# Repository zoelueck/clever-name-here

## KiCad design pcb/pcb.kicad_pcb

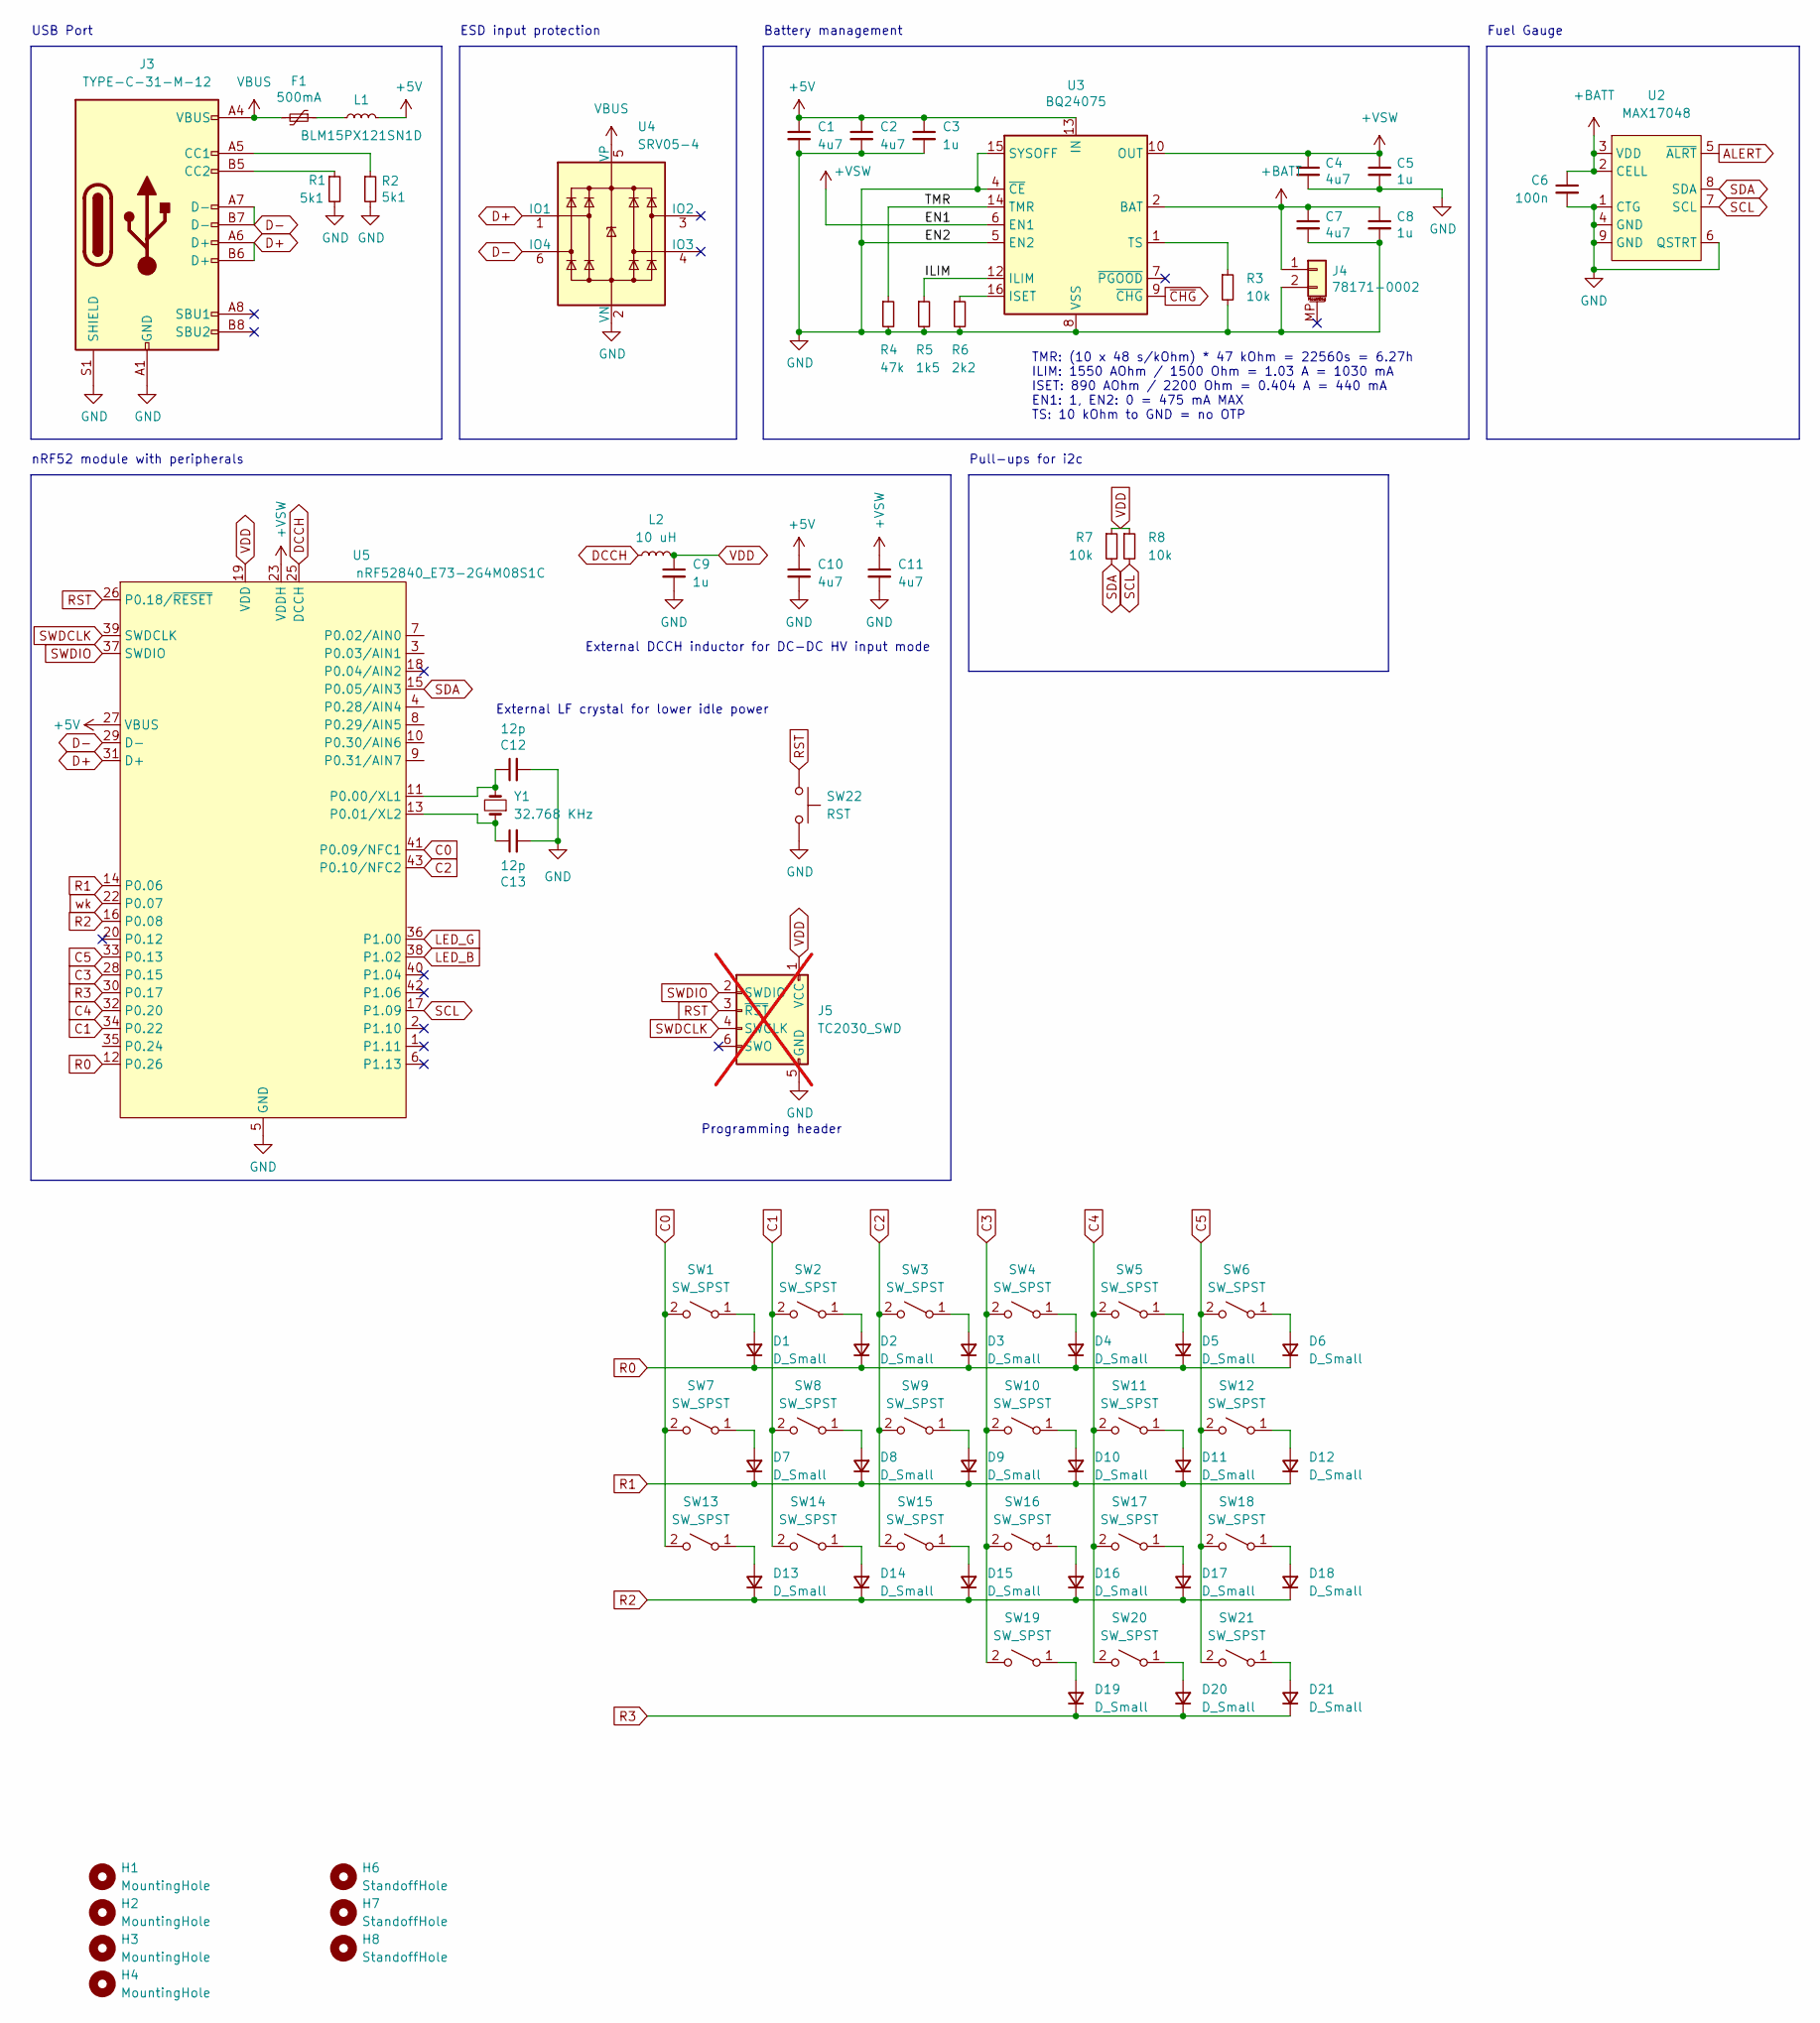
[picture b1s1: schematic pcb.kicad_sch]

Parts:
C1, C2, C4, C7, C10, C11: 4u7; C_0402_1005Metric; LCSC C23733
C3, C5, C8, C9: 1u; C_0402_1005Metric; LCSC C52923
C6: 100n; C_0402_1005Metric; LCSC C307331
C12, C13: 12p; C_0402_1005Metric; LCSC C1547
D1, D2, D3, D4, D5, D6, D7, D8, D9, D10, D11, D12, D13, D14, D15, D16, D17, D18, D19, D20, D21: D_Small; Diode_TH_SMD_DUAL
F1: 500mA; Fuse_0603_1608Metric; LCSC C883095
H1, H2, H3, H4: MountingHole; Hole_4.2mm
H6, H7, H8: StandoffHole; Hole_2.2mm
J3: TYPE-C-31-M-12; USB_C_Receptacle_HRO_TYPE-C-31-M-12; LCSC C165948
J4: 78171-0002; Molex_Pico-EZmate_78171-0002_1x02-1MP_P1.20mm_Vertical; LCSC C505023
J5: TC2030_SWD; CON_TC2030_outlined; not fitted
L1: BLM15PX121SN1D; L_0402_1005Metric; LCSC C88970
L2: 10 uH; L_0603_1608Metric; LCSC C92982
R1, R2: 5k1; R_0402_1005Metric; LCSC C25905
R3, R7, R8: 10k; R_0402_1005Metric; LCSC C25744
R4: 47k; R_0402_1005Metric; LCSC C25792
R5: 1k5; R_0402_1005Metric; LCSC C25867
R6: 2k2; R_0402_1005Metric; LCSC C25879
SW1, SW2, SW3, SW4, SW5, SW6, SW7, SW8, SW9, SW10, SW11, SW12, SW13, SW14, SW15, SW16, SW17, SW18, SW19, SW20, SW21: SW_SPST; KS-27_KS-33_Hotswap_1U_DUAL
SW22: RST; SW_T1A2QR; LCSC C100056
U2: MAX17048; DFN-8-1EP_2x2mm_P0.5mm_EP0.7x1.3mm; LCSC C2682616
U3: BQ24075; VQFN-16-1EP_3x3mm_P0.5mm_EP1.6x1.6mm; LCSC C15464
U4: SRV05-4; SOT-23-6-routable; LCSC C7420376
U5: nRF52840_E73-2G4M08S1C; LCSC C356849
Y1: 32.768 KHz; Crystal_SMD_2012-2Pin_2.0x1.2mm; LCSC C55208

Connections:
+5V: C1.1, C2.1, C3.1, C10.1, L1.2, U3.13 (IN), U5.27 (VBUS)
+BATT: C6.1, C7.1, C8.1, J4.1, U2.2 (CELL), U2.3 (VDD), U3.2 (BAT), U3.3 (BAT)
+VSW: C4.1, C5.1, C11.1, U3.6 (EN1), U3.10 (OUT), U3.11 (OUT), U5.23 (VDDH)
/ILIM: R5.1, U3.12 (ILIM)
/TMR: R4.1, U3.14 (TMR)
ALERT: U2.5 (~ALRT)
C0: SW1.2 (B), SW7.2 (B), SW13.2 (B), U5.41 (P0.09/NFC1)
C1: SW2.2 (B), SW8.2 (B), SW14.2 (B), U5.34 (P0.22)
C2: SW3.2 (B), SW9.2 (B), SW15.2 (B), U5.43 (P0.10/NFC2)
C3: SW4.2 (B), SW10.2 (B), SW16.2 (B), SW19.2 (B), U5.28 (P0.15)
C4: SW5.2 (B), SW11.2 (B), SW17.2 (B), SW20.2 (B), U5.32 (P0.20)
C5: SW6.2 (B), SW12.2 (B), SW18.2 (B), SW21.2 (B), U5.33 (P0.13)
D+: J3.A6 (D+), J3.B6 (D+), U4.1 (IO1), U5.31 (D+)
D-: J3.A7 (D-), J3.B7 (D-), U4.6 (IO4), U5.29 (D-)
DCCH: L2.1, U5.25 (DCCH)
GND: C1.2, C2.2, C3.2, C4.2, C5.2, C6.2, C7.2, C8.2, C9.2, C10.2, C11.2, C12.2, C13.2, J3.A1 (GND), J3.A12 (GND), J3.B1 (GND), J3.B12 (GND), J3.S1 (SHIELD), J4.2, J5.5 (GND), R1.2, R2.2, R3.2, R4.2, R5.2, R6.2, SW22.2, U2.1 (CTG), U2.4 (GND), U2.6 (QSTRT), U2.9 (GND), U3.4 (~CE), U3.5 (EN2), U3.8 (VSS), U3.15 (SYSOFF), U3.17 (VSS), U4.2 (VN), U5.5 (GND), U5.21 (GND), U5.24 (GND)
LED_B: U5.38 (P1.02)
LED_G: U5.36 (P1.00)
unnamed: D1.2 (A), SW1.1 (A)
unnamed: D2.2 (A), SW2.1 (A)
unnamed: D3.2 (A), SW3.1 (A)
unnamed: D4.2 (A), SW4.1 (A)
unnamed: D5.2 (A), SW5.1 (A)
unnamed: D6.2 (A), SW6.1 (A)
unnamed: D7.2 (A), SW7.1 (A)
unnamed: D8.2 (A), SW8.1 (A)
unnamed: D9.2 (A), SW9.1 (A)
unnamed: D10.2 (A), SW10.1 (A)
unnamed: D11.2 (A), SW11.1 (A)
unnamed: D12.2 (A), SW12.1 (A)
unnamed: D13.2 (A), SW13.1 (A)
unnamed: D14.2 (A), SW14.1 (A)
unnamed: D15.2 (A), SW15.1 (A)
unnamed: D16.2 (A), SW16.1 (A)
unnamed: D17.2 (A), SW17.1 (A)
unnamed: D18.2 (A), SW18.1 (A)
unnamed: D19.2 (A), SW19.1 (A)
unnamed: D20.2 (A), SW20.1 (A)
unnamed: D21.2 (A), SW21.1 (A)
unnamed: F1.1, L1.1
unnamed: J3.A5 (CC1), R2.1
unnamed: J3.B5 (CC2), R1.1
unnamed: R6.1, U3.16 (ISET)
unnamed: R3.1, U3.1 (TS)
unnamed: C12.1, U5.11 (P0.00/XL1), Y1.2
unnamed: C13.1, U5.13 (P0.01/XL2), Y1.1
R0: D1.1 (K), D2.1 (K), D3.1 (K), D4.1 (K), D5.1 (K), D6.1 (K), U5.12 (P0.26)
R1: D7.1 (K), D8.1 (K), D9.1 (K), D10.1 (K), D11.1 (K), D12.1 (K), U5.14 (P0.06)
R2: D13.1 (K), D14.1 (K), D15.1 (K), D16.1 (K), D17.1 (K), D18.1 (K), U5.16 (P0.08)
R3: D19.1 (K), D20.1 (K), D21.1 (K), U5.30 (P0.17)
RST: J5.3 (~RST), SW22.1, U5.26 (P0.18/~RESET)
SCL: R8.2, U2.7 (SCL), U5.17 (P1.09)
SDA: R7.2, U2.8 (SDA), U5.15 (P0.05/AIN3)
SWDCLK: J5.4 (SWCLK), U5.39 (SWDCLK)
SWDIO: J5.2 (SWDIO), U5.37 (SWDIO)
VBUS: F1.2, J3.A4 (VBUS), J3.A9 (VBUS), J3.B4 (VBUS), J3.B9 (VBUS), U4.5 (VP)
VDD: C9.1, J5.1 (VCC), L2.2, R7.1, R8.1, U5.19 (VDD)
wk: U5.22 (P0.07)
~CHG: U3.9 (~CHG)

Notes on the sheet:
Fuel Gauge
Pull-ups for i2c
Programming header
USB Port
External LF crystal for lower idle power
Battery management
TMR: (10 x 48 s/kOhm) * 47 kOhm = 22560s = 6.27h ILIM: 1550 AOhm / 1500 Ohm = 1.03 A = 1030 mA ISET: 890 AOhm / 2200 Ohm = 0.404 A = 440 mA EN1: 1, EN2: 0 = 475 mA MAX TS: 10 kOhm to GND = no OTP
nRF52 module with peripherals
External DCCH inductor for DC-DC HV input mode
ESD input protection

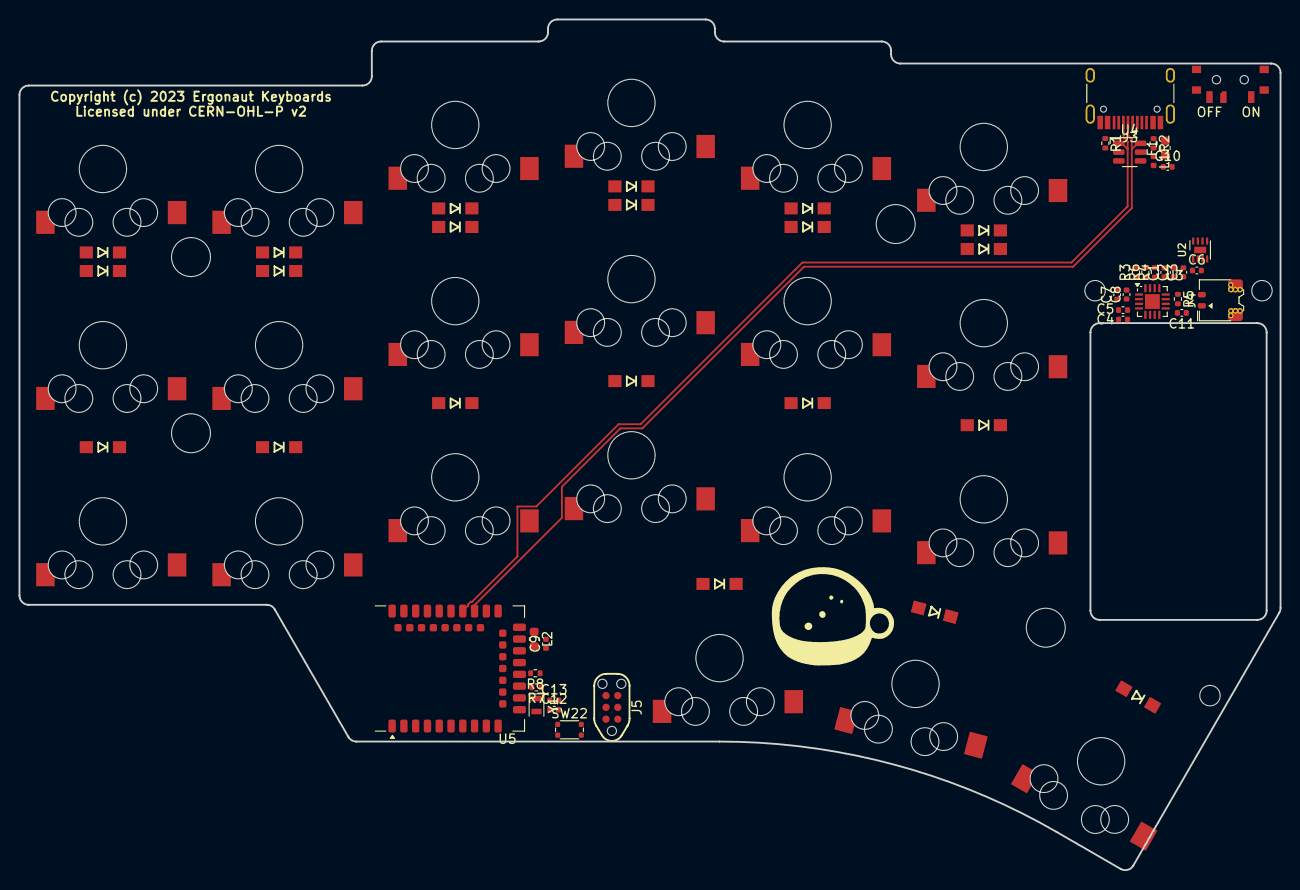
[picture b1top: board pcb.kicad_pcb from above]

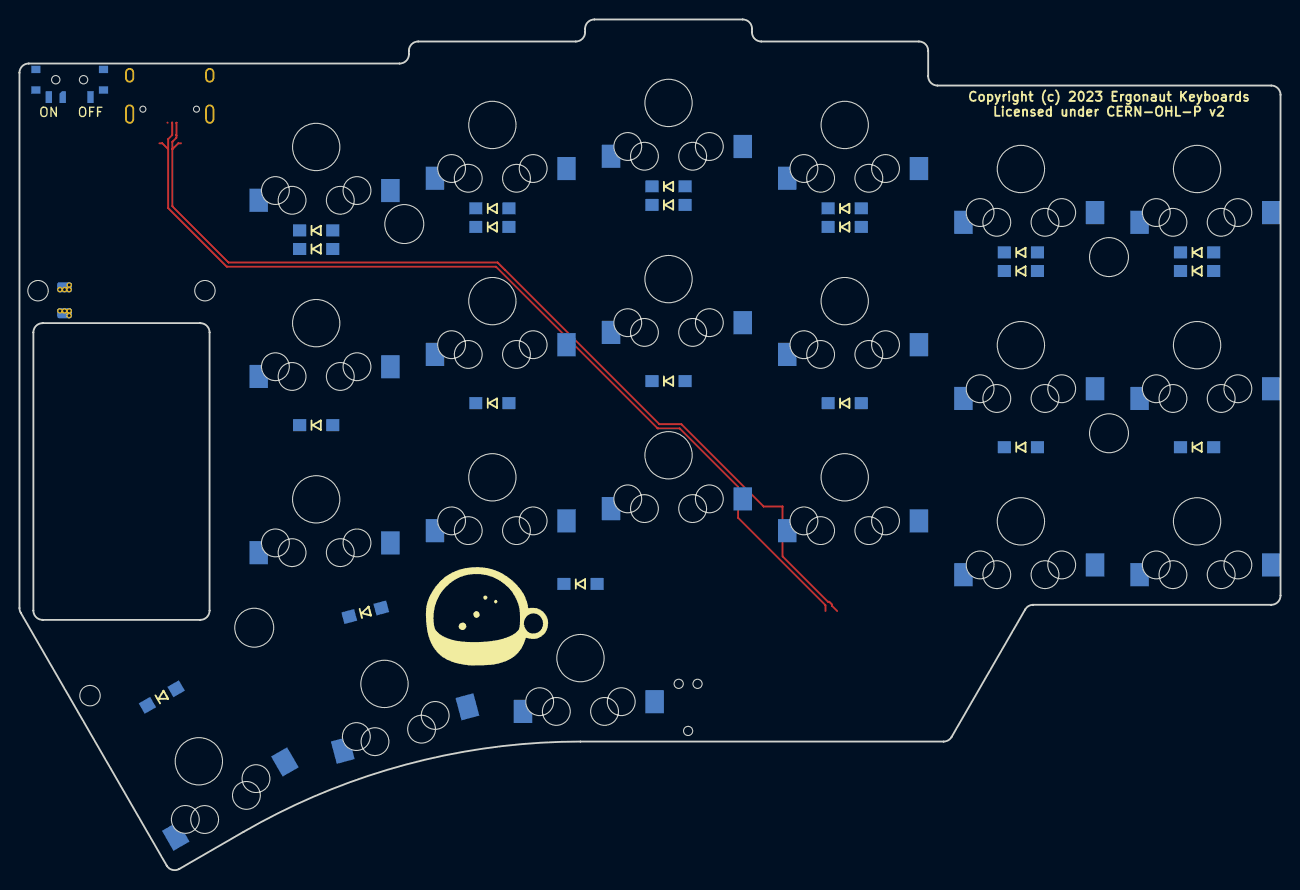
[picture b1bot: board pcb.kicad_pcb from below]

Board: 2 copper layers, 136.0 x 91.7 mm, 83 parts (22 on the bottom side), 54 nets.

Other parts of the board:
PWR1: SW_SPDT; MSK-12C02_DUAL

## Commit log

2025-05-21 backup

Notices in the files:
pcb/pcb.kicad_pcb:
Copyright (c) 2023 Ergonaut Keyboards
Licensed under CERN-OHL-P v2
